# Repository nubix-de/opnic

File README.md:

# What is OPNIC?

OPNIC is an artificial project name... It is a low-cost hardware platform designed to show what is possible with a budget of €6 for electronic components. The nubix engineers took on the challenge of developing a universally usable platform with this limited budget. The hardware consists of:
- MCU PR2040 dual core Cortex M0+ @ 125 MHz
- 264 kByte RAM and 512 kByte Flash
- 160 x 128 RGB TFT LCD
- 4 x capacitive touch buttons
- RGB LED
- 3-axis gyroscope, 3-axis accelerometer MPU6050
- connectivity: USB, SWD, UART or I2C, 3 x GPIO /w ADC
- USB powered
  
...which is quite a lot for just 6€.<br>
The even bigger challenge was to bring a smoothly playable arcade game to this hardware, which we managed to do quite well. It's a great pleasure to see what incredible performance can be achieved with inexpensive electronics if you develop the right software for it.<br>
We are making the software, libraries and hardware developed for this available to the general public as open source (BSD3 license) and invite you to experiment, expand and use this platform. We are very excited to see what applications you come up with for this platform.

# Quick-start

1. fit a 2¢ euro coin into BOOTSEL to switch into programming mode
2. connect the board via micro USB cable to the computer
3. remove the coin
4. run: `./build.sh -+ snake release uf2`

For more information, read the [development](DEVELOPMENT.md) file.

# Folder structure

Folder structure is the following:

- `doc`: contains the documentation
- `hardware`: contains the EAGLE files
- `firmware`: contains the firmware-related folders, like `micropython` and
  `cpp`

Each folder inside the `micropython` and `cpp` directories contains the so
called "projects". A project can be a library with a test script or a target
application.

Note on project compilation: if you don't have the pico-sdk installed on your
system, it will download from the Internet before compiling.

# How to run the build script

All `build.sh` files need to know which project to compile / run. For example
`./build.sh touch [options]` will tell it to use the `touch` project. For more
information, please use the `-h` option.

**Please note that for OPNIC Board Rev. A, programming with Micropython is
unavailable.**

# Thank you

Thank you Ted Rossin for allowing us to make usage and small changes to your
[TFT Display GUI on Raspberry Pi
Pico](https://sites.google.com/site/tedrossin/home/electronics/raspberry-pi-pico#h.tnj1ljp6rrfh)
project.

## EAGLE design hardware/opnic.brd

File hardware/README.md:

The board was developed using Eagle (Easy Applicable Graphical Layout Editor).

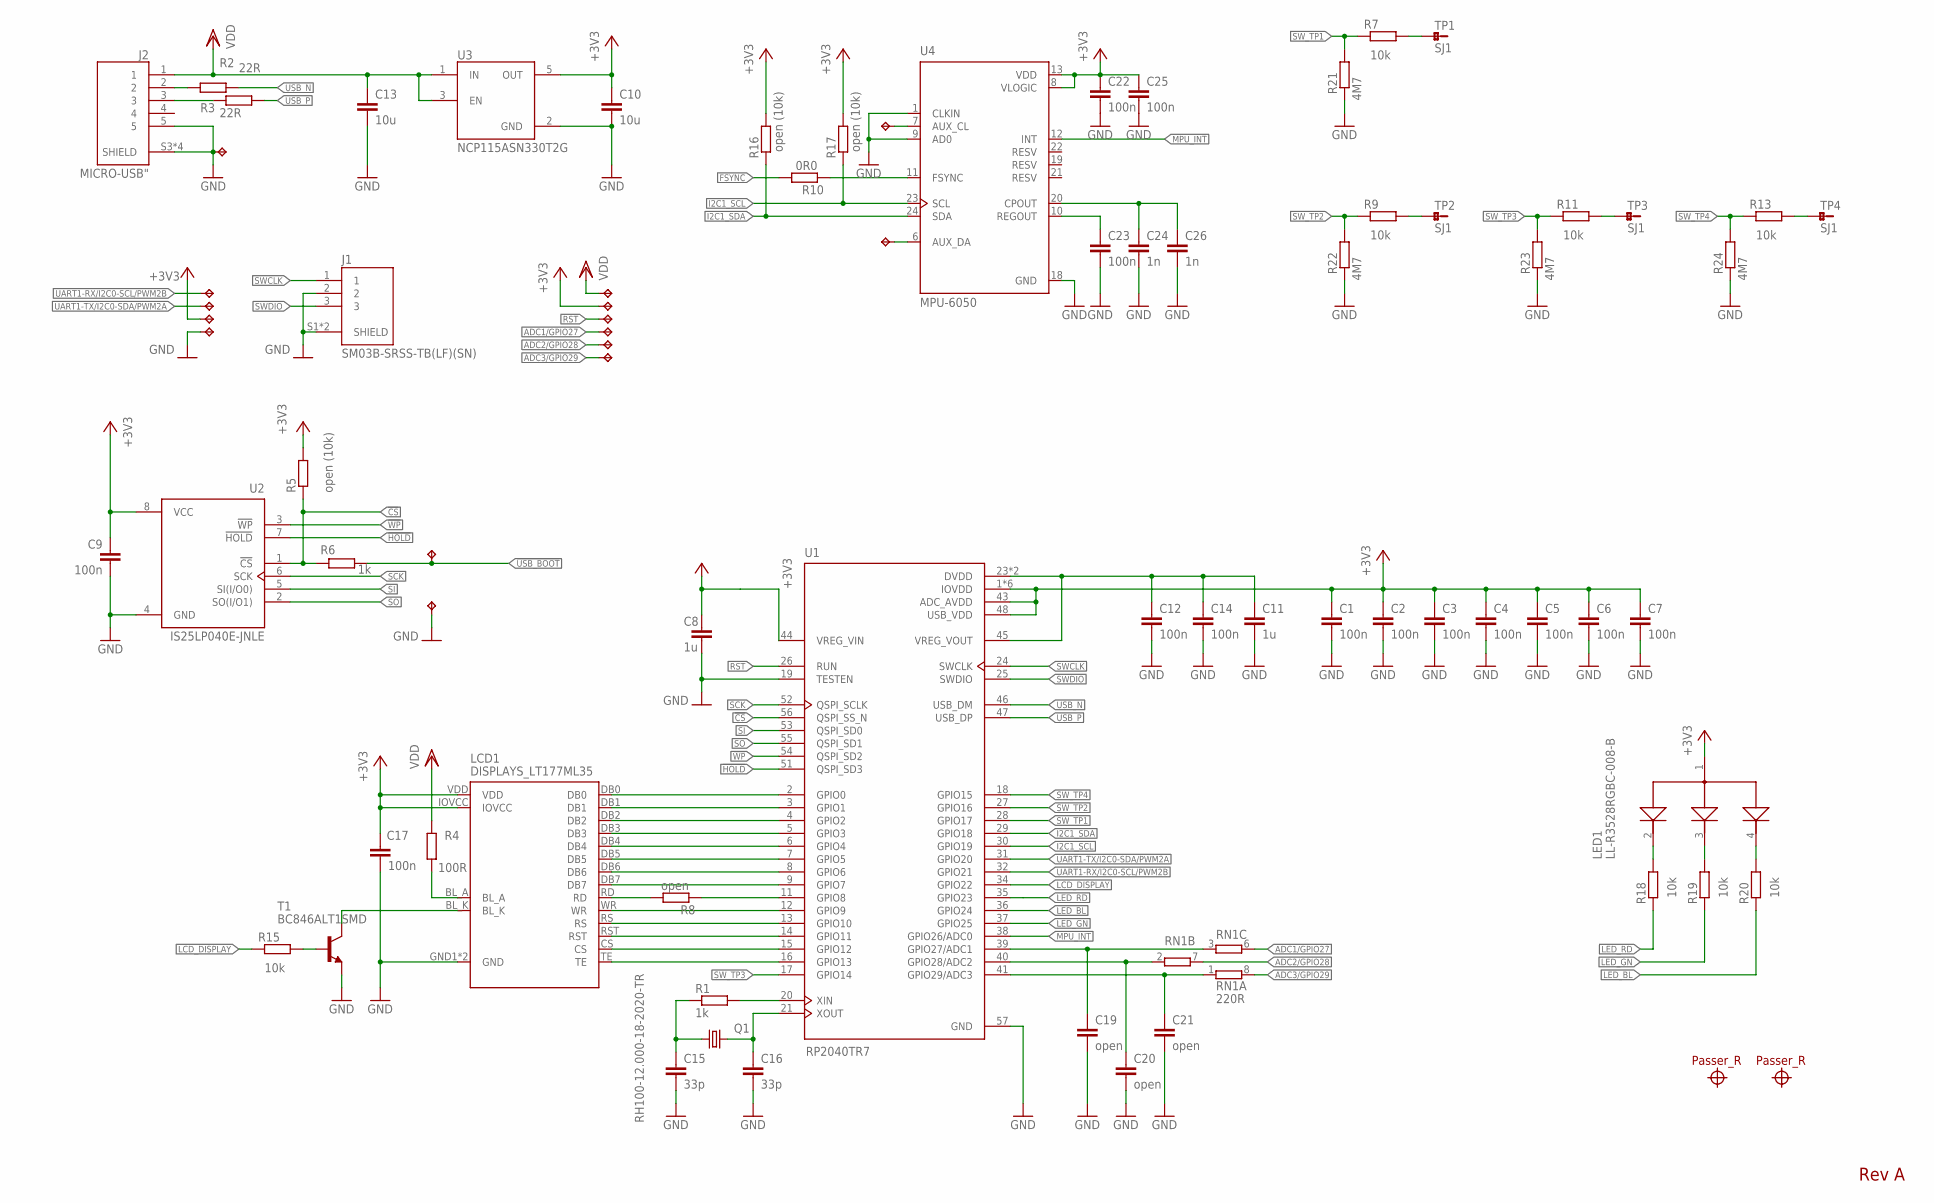
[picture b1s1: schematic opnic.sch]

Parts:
3V3: TPTP06SQ; TP06SQ
C1, C2, C3, C4, C5, C6, C7, C9, C12, C14, C17, C22, C23, C25: 100n; C0603
C8, C11: 1u; C0805
C10, C13: 10u; C1206
C15, C16: 33p; C0603
C19, C20, C21: open; C0603
C24, C26: 1n; C0603
CL: TPTP15SQ; TP15SQ
DA: TPTP15SQ; TP15SQ
GND: TPTP06SQ; TP06SQ
J1: SM03B-SRSS-TB(LF)(SN); JST_SM03B-SRSS-TB(LF)(SN)
J2: MICRO-USB"; MICRO-USB_MIDMOUNT
LCD1: DISPLAYS_LT177ML35
LED1: LL-R3528RGBC-008-B; LED_LL-R3528RGBC-008-B
P27, P28, P29: TPTP06SQ; TP06SQ
Q1: RH100-12.000-18-2020-TR; 3.2X2.5_KX-7
R1, R6: 1k; R0603
R2, R3: 22R; R0603
R4: 100R; R0603
R5, R16, R17: open (10k); R0603
R7, R9, R11, R13, R15, R18, R19, R20: 10k; R0603
R8: open; R0603
R10: 0R0; R0603
R21, R22, R23, R24: 4M7; R1206
RN1: 220R; 0603-ARC
RST: TPTP06SQ; TP06SQ
SCL: TPTP06SQ; TP06SQ
SDA: TPTP06SQ; TP06SQ
T1: BC846ALT1SMD; SOT23
TP1, TP2, TP3, TP4: SJ1; PAD1X1
TP9, TP10: TPPAD1-17; P1-17
TP11: TPTP06SQ; TP06SQ
U1: RP2040TR7; QFN40P700X700X90-57N
U2: IS25LP040E-JNLE; SOIC127P599X175-8N
U3: NCP115ASN330T2G; SOT95P280X145-5N
U4: MPU-6050; QFN50P400X400X95-24N
U$1, U$2: PASSER_R; PASSER_RUND
VCC1, VCC2: TPTP06SQ; TP06SQ

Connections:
!CS: R5.1, R6.2, U1.56 (QSPI_SS_N), U2.1 (!CS)
!HOLD: U1.51 (QSPI_SD3), U2.7 (!HOLD)
!USB_BOOT: R6.1, TP9.TP
!WP: U1.54 (QSPI_SD2), U2.3 (!WP)
+3V3: 3V3.TP, C1.1, C2.1, C3.1, C4.1, C5.1, C6.1, C7.1, C8.1, C9.1, C10.1, C17.1, C22.1, C25.1, LCD1.IOVCC, LCD1.VDD, LED1.1 (COMM_ANODE), R5.2, R16.2, R17.2, U1.1 (IOVDD), U1.10 (IOVDD), U1.22 (IOVDD), U1.33 (IOVDD), U1.42 (IOVDD), U1.43 (ADC_AVDD), U1.44 (VREG_VIN), U1.48 (USB_VDD), U1.49 (IOVDD), U2.8 (VCC), U3.5 (OUT), U4.8 (VLOGIC), U4.13 (VDD), VCC1.TP
ADC1/GPIO27: P27.TP, RN1.6 (2)
ADC2/GPIO28: P28.TP, RN1.7 (2)
ADC3/GPIO29: P29.TP, RN1.8 (2)
AUX_CL: CL.TP, U4.7 (AUX_CL)
AUX_DA: DA.TP, U4.6 (AUX_DA)
BL: LED1.4 (CATHODE_BLUE), R20.2
BL_A: LCD1.BL_A, R4.1
BL_K: LCD1.BL_K, T1.3 (C)
CPOUT: C24.1, C26.1, U4.20 (CPOUT)
CS: LCD1.CS, U1.15 (GPIO12)
DB0: LCD1.DB0, U1.2 (GPIO0)
DB1: LCD1.DB1, U1.3 (GPIO1)
DB2: LCD1.DB2, U1.4 (GPIO2)
DB3: LCD1.DB3, U1.5 (GPIO3)
DB4: LCD1.DB4, U1.6 (GPIO4)
DB5: LCD1.DB5, U1.7 (GPIO5)
DB6: LCD1.DB6, U1.8 (GPIO6)
DB7: LCD1.DB7, U1.9 (GPIO7)
DM: J2.2, R2.1
DP: J2.3, R3.1
DVDD: C11.1, C12.1, C14.1, U1.23 (DVDD), U1.45 (VREG_VOUT), U1.50 (DVDD)
FSYNC: R8.1, R10.2, U1.11 (GPIO8)
GN: LED1.3 (CATHODE_GREEN), R19.2
GND: C1.2, C2.2, C3.2, C4.2, C5.2, C6.2, C7.2, C8.2, C9.2, C10.2, C11.2, C12.2, C13.2, C14.2, C15.2, C16.2, C17.2, C19.2, C20.2, C21.2, C22.2, C23.2, C24.2, C25.2, C26.2, GND.TP, J1.2, J1.S1 (SHIELD), J1.S2 (SHIELD), J2.5, J2.S3 (SHIELD), J2.S4 (SHIELD), J2.S5 (SHIELD), J2.S6 (SHIELD), LCD1.GND1 (GND), LCD1.GND2 (GND), R21.1, R22.1, R23.1, R24.1, T1.2 (E), TP10.TP, TP11.TP, U1.19 (TESTEN), U1.57 (GND), U2.4 (GND), U3.2 (GND), U4.1 (CLKIN), U4.9 (AD0), U4.18 (GND)
GPIO27: C19.1, RN1.3 (1), U1.39 (GPIO27/ADC1)
GPIO28: C20.1, RN1.2 (1), U1.40 (GPIO28/ADC2)
GPIO29: C21.1, RN1.1, U1.41 (GPIO29/ADC3)
I2C1_SCL: R17.1, U1.30 (GPIO19), U4.23 (SCL)
I2C1_SDA: R16.1, U1.29 (GPIO18), U4.24 (SDA)
LCD_DISPLAY: R15.1, U1.34 (GPIO22)
LED_BL: R20.1, U1.36 (GPIO24)
LED_GN: R19.1, U1.37 (GPIO25)
LED_RD: R18.1, U1.35 (GPIO23)
MPU_FSYNC: R10.1, U4.11 (FSYNC)
MPU_INT: U1.38 (GPIO26/ADC0), U4.12 (INT)
unnamed: C15.1, Q1.1, R1.1
unnamed: C16.1, Q1.3 (2), U1.21 (XOUT)
unnamed: LCD1.RD, R8.2
unnamed: R1.2, U1.20 (XIN)
unnamed: R15.2, T1.1 (B)
RED: LED1.2 (CATHODE_RED), R18.2
REGOUT: C23.1, U4.10 (REGOUT)
RS: LCD1.RS, U1.13 (GPIO10)
RST: RST.TP, U1.26 (RUN)
RST_DISPLAY: LCD1.RST, U1.14 (GPIO11)
SCK: U1.52 (QSPI_SCLK), U2.6 (SCK)
SI: U1.53 (QSPI_SD0), U2.5 (SI(I/O0))
SO: U1.55 (QSPI_SD1), U2.2 (SO(I/O1))
SWCLK: J1.1, U1.24 (SWCLK)
SWDIO: J1.3, U1.25 (SWDIO)
SW_TP1: R7.1, R21.2, U1.28 (GPIO17)
SW_TP2: R9.1, R22.2, U1.27 (GPIO16)
SW_TP3: R11.1, R23.2, U1.17 (GPIO14)
SW_TP4: R13.1, R24.2, U1.18 (GPIO15)
TE: LCD1.TE, U1.16 (GPIO13)
TP1: R7.2, TP1.P$1
TP2: R9.2, TP2.P$1
TP3: R11.2, TP3.P$1
TP4: R13.2, TP4.P$1
UART1-RX/I2C0-SCL/PWM2B: SCL.TP, U1.32 (GPIO21)
UART1-TX/I2C0-SDA/PWM2A: SDA.TP, U1.31 (GPIO20)
USB_N: R2.2, U1.46 (USB_DM)
USB_P: R3.2, U1.47 (USB_DP)
VDD: C13.1, J2.1, R4.2, U3.1 (IN), U3.3 (EN), VCC2.TP
WR: LCD1.WR, U1.12 (GPIO9)

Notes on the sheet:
Rev A

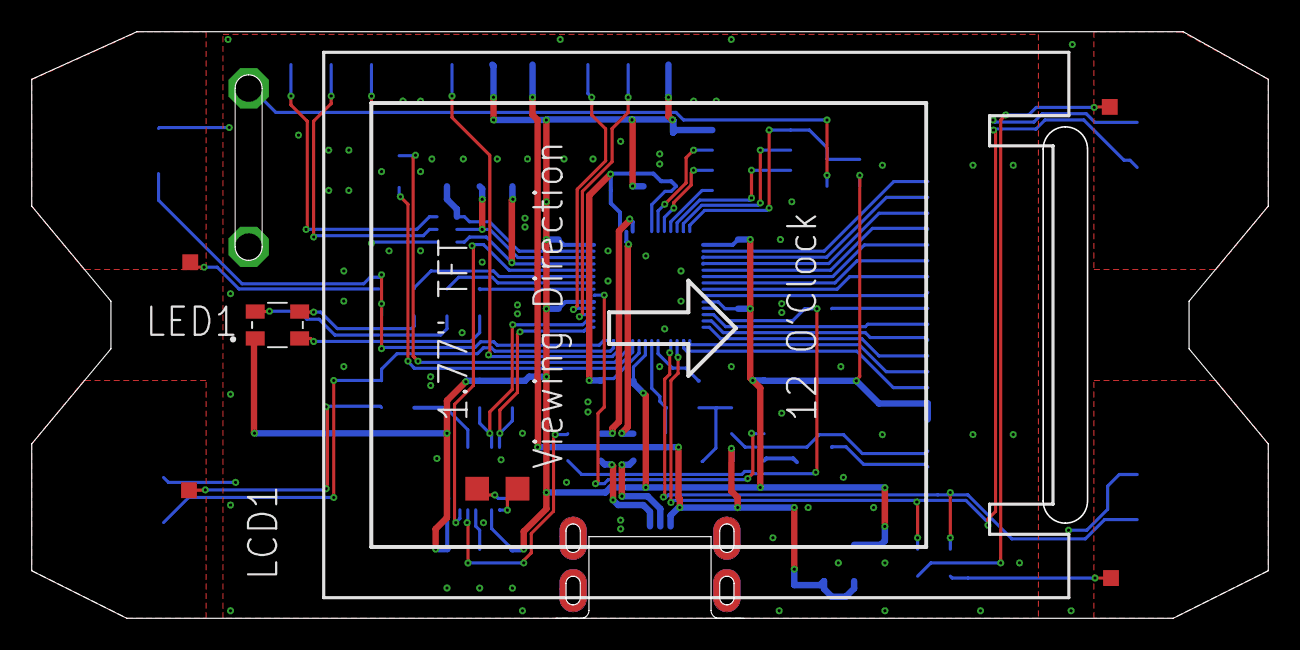
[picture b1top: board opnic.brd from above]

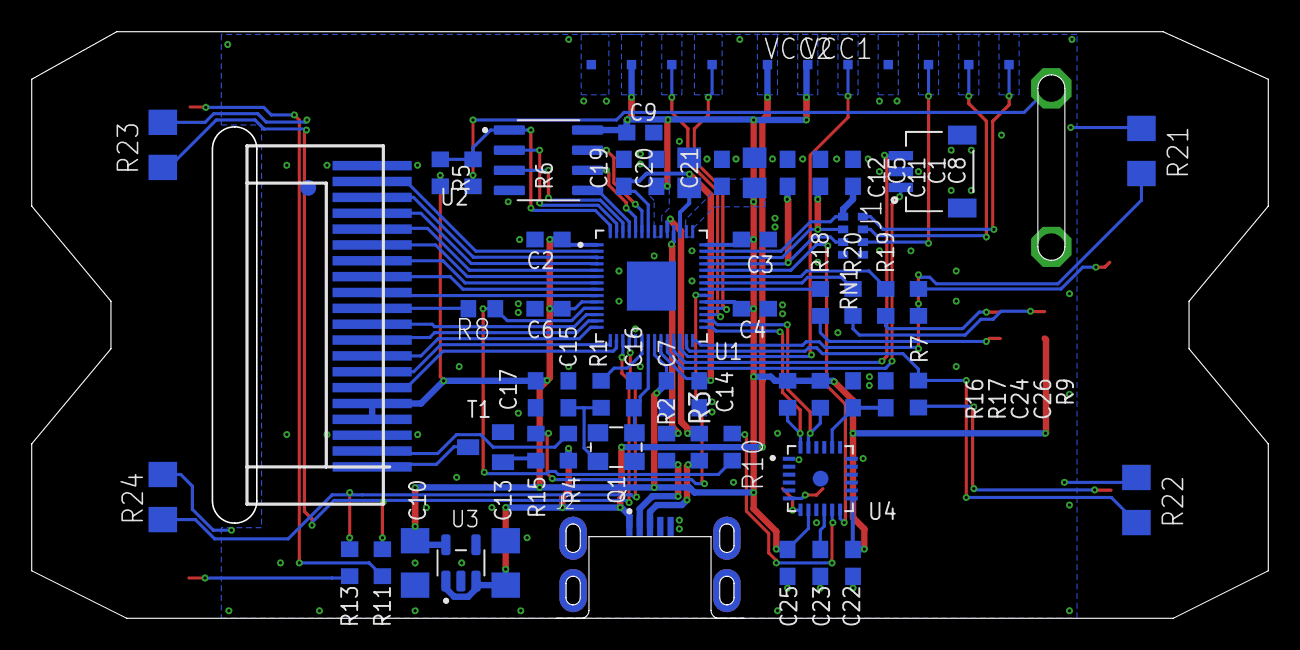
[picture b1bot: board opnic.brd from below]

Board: 2 copper layers, 78.0 x 37.0 mm, 79 parts (69 on the bottom side), 70 nets.

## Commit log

2023-11-27 the initial commit and at the same time the first version of OPNIC
2023-11-29 Adjusted some content of the README.md file related to the snake game
2023-12-04 update README to introduce OPNIC

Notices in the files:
parts and their libraries:
crystal-geyer_V1_0: Copyright: Geyer-Electronic
